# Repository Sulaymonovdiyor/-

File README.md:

### Название проекта: Разработка конструкторской документации с применением программных средств

#### Описание проекта:
Проект направлен на разработку конструкторской документации для устройства с использованием программных средств. Процесс включает выполнение следующих этапов:

1. **Расчет элементов схемы:**
   - Провести расчёт элементов схемы в соответствии с индивидуальным вариантом, округляя значения к ближайшему стандартному значению ряда Е24.

2. **Моделирование схемы:**
   - Провести моделирование работы схемы с использованием программного пакета NI MultiSIM.
   - Подготовить графики АЧХ (амплитудно-частотной характеристики) и ФЧХ (фазово-частотной характеристики).

3. **Проектирование электрической схемы и печатной платы:**
   - Нарисовать электрическую принципиальную схему устройства с использованием пакета KiCAD.
   - Выполнить трассировку печатной платы в пакете KiCAD.

4. **Перенос данных и создание сборки:**
   - Изучить методику переноса данных из пакета KiCAD в пакет Компас 3D.
   - Создать сборку печатного узла в пакете Компас 3D.

5. **Подготовка 3D-моделей элементов:**
   - Подготовить 3D-модели элементов, входящих в состав сборки печатной платы (резистор, конденсатор, микросхема, разъём, плата).

6. **Создание ассоциативных чертежей:**
   - На основе сборки создать двухмерные ассоциативные чертежи печатного узла в соответствии с ЕСКД.

#### Пояснительная записка:
Пояснительная записка должна включать следующие разделы:

- Результаты расчёта элементов схемы и округления к ближайшему стандартному значению ряда Е24.
- Результаты моделирования схемы в пакете MultiSIM с графиками АЧХ и ФЧХ.
- Описание работы в пакете KiCAD с индивидуальными снимками экрана.
- Описание методики переноса данных из KiCAD в Компас-3D и разнесения их по слоям.
- Описание создания деталей и сборки устройства с указанием используемых привязок.
- Описание создания ассоциативного двухмерного чертежа.

#### Чертежи (выполняются в соответствии с ЕСКД):
- Электрическая принципиальная схема и перечень элементов (из KiCAD).
- Чертёж печатной платы (из Kомпас-3D).
- Фотореалистичный рисунок печатного узла.
- Сборочный чертёж печатной платы с элементами и спецификацией.

#### Разработчик:
- Имя: [диёр]
- Контактная информация: [https://vk.me/furusatoo]

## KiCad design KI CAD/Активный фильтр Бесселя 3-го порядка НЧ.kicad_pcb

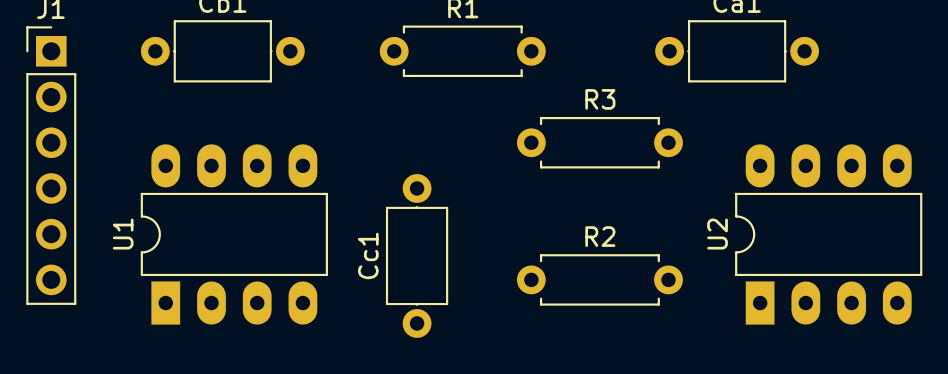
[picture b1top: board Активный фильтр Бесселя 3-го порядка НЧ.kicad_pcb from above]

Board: 2 copper layers, 9 parts (0 on the bottom side), 8 nets, no tracks yet.

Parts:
Ca1: 1.6n; C_Axial_L5.1mm_D3.1mm_P7.50mm_Horizontal
Cb1: 9.1n; C_Axial_L5.1mm_D3.1mm_P7.50mm_Horizontal
Cc1: 1.3n; C_Axial_L5.1mm_D3.1mm_P7.50mm_Horizontal
J1: Conn_01x06_Male; PinHeader_1x06_P2.54mm_Vertical
R1, R2, R3: 7.5k; R_Axial_DIN0207_L6.3mm_D2.5mm_P7.62mm_Horizontal
U1, U2: LM741; DIP-8_W7.62mm_LongPads

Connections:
GND: Cb1.2, Cc1.2, J1.2, J1.4, J1.6, U1.4, U2.4
unnamed: Ca1.1, R3.2, U1.2, U1.6
unnamed: Ca1.2, R1.1, R2.2
unnamed: Cb1.1, R2.1, U1.3
unnamed: Cc1.1, R3.1, U2.3
unnamed: J1.1, R1.2
unnamed: J1.3, U2.2, U2.6
VCC: J1.5, U1.7, U2.7
